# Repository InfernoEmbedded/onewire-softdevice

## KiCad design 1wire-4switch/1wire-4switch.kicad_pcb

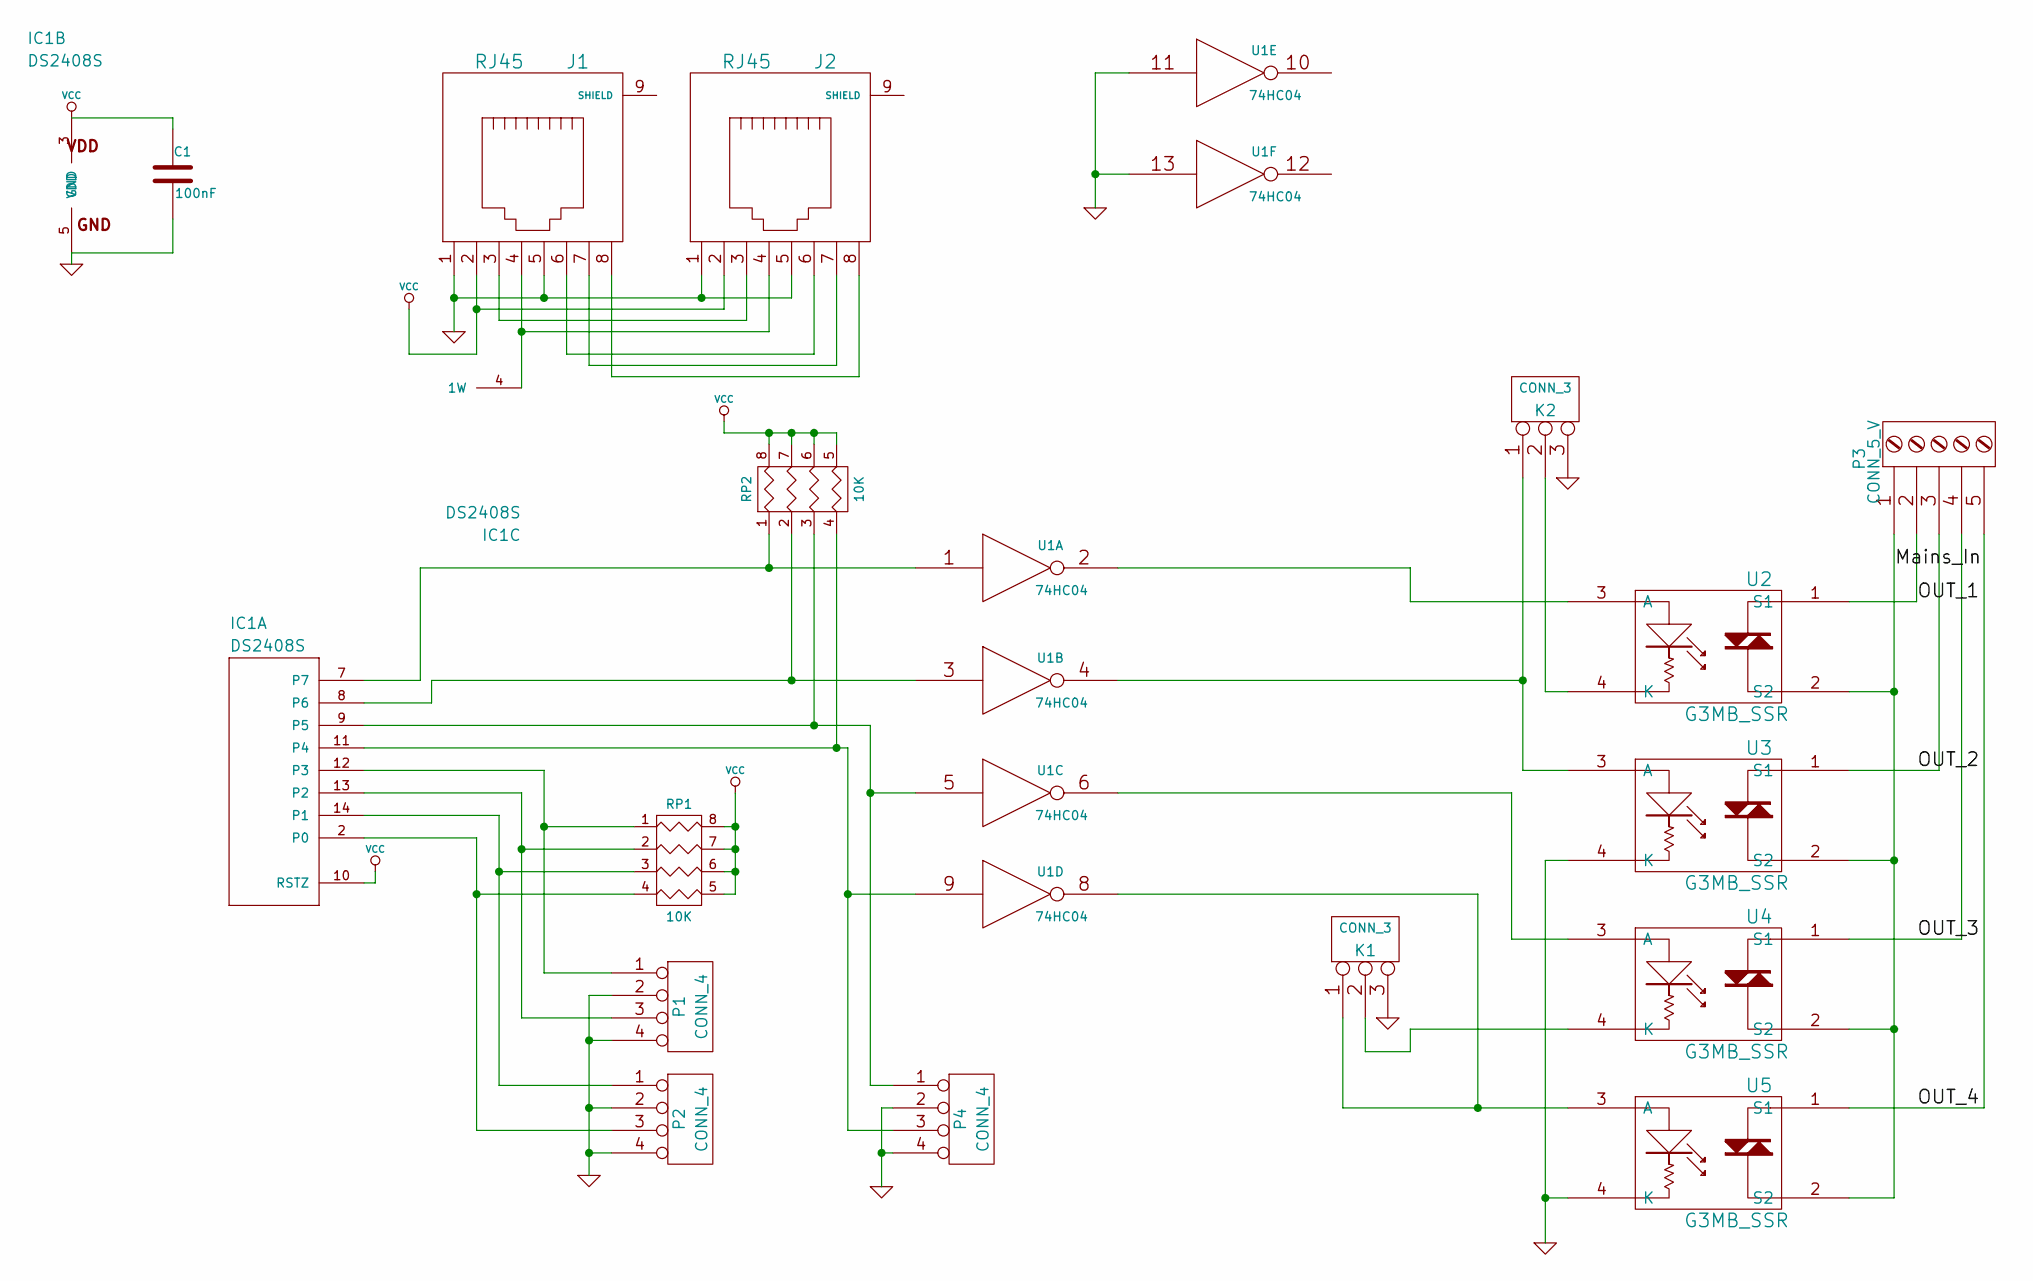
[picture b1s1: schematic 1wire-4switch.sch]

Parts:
C1: 100nF
IC1: DS2408S; 1wire-SO16
J1, J2: RJ45
K1, K2: CONN_3
P1, P2, P4: CONN_4
P3: CONN_5_V
RP1, RP2: 10K
U1: 74HC04
U2, U3, U4, U5: G3MB_SSR

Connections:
/Mains_In: P3.1, U2.2 (S2), U3.2 (S2), U4.2 (S2), U5.2 (S2)
/OUT_1: P3.2, U2.1 (S1)
/OUT_2: P3.3, U3.1 (S1)
/OUT_3: P3.4, U4.1 (S1)
/OUT_4: P3.5, U5.1 (S1)
GND: C1.2, IC1.5 (GND), J1.1, J1.5, J2.1, J2.5, K1.3, K2.3, P1.2, P1.4, P2.2, P2.4, P4.2, P4.4, U1.7 (GND), U1.11, U1.13, U3.4 (K), U5.4 (K)
unnamed: K1.1, U1.8, U5.3 (A)
unnamed: U1.6, U4.3 (A)
unnamed: IC1.7, RP2.1, U1.1
unnamed: K1.2 (PM), U4.4 (K)
unnamed: K2.1, U1.4, U3.3 (A)
unnamed: U1.2, U2.3 (A)
unnamed: K2.2 (PM), U2.4 (K)
unnamed: IC1.11 (P4), P4.3, RP2.4, U1.9
unnamed: IC1.9 (P5), P4.1, RP2.3, U1.5
unnamed: IC1.8 (P6), RP2.2, U1.3
unnamed: J1.8, J2.8
unnamed: J1.7, J2.7
unnamed: J1.6, J2.6
unnamed: IC1.4 (1W), J1.4, J2.4
unnamed: IC1.12 (P3), P1.1, RP1.1
unnamed: J1.3, J2.3
unnamed: IC1.2 (P0), P2.3, RP1.4
unnamed: IC1.14 (P1), P2.1, RP1.3
unnamed: IC1.13 (P2), P1.3, RP1.2
VCC: C1.1, IC1.3 (VDD), IC1.10 (RSTZ), J1.2, J2.2, RP1.5 (R4), RP1.6 (R3), RP1.7 (R2), RP1.8 (R1), RP2.5 (R4), RP2.6 (R3), RP2.7 (R2), RP2.8 (R1), U1.14 (VCC)

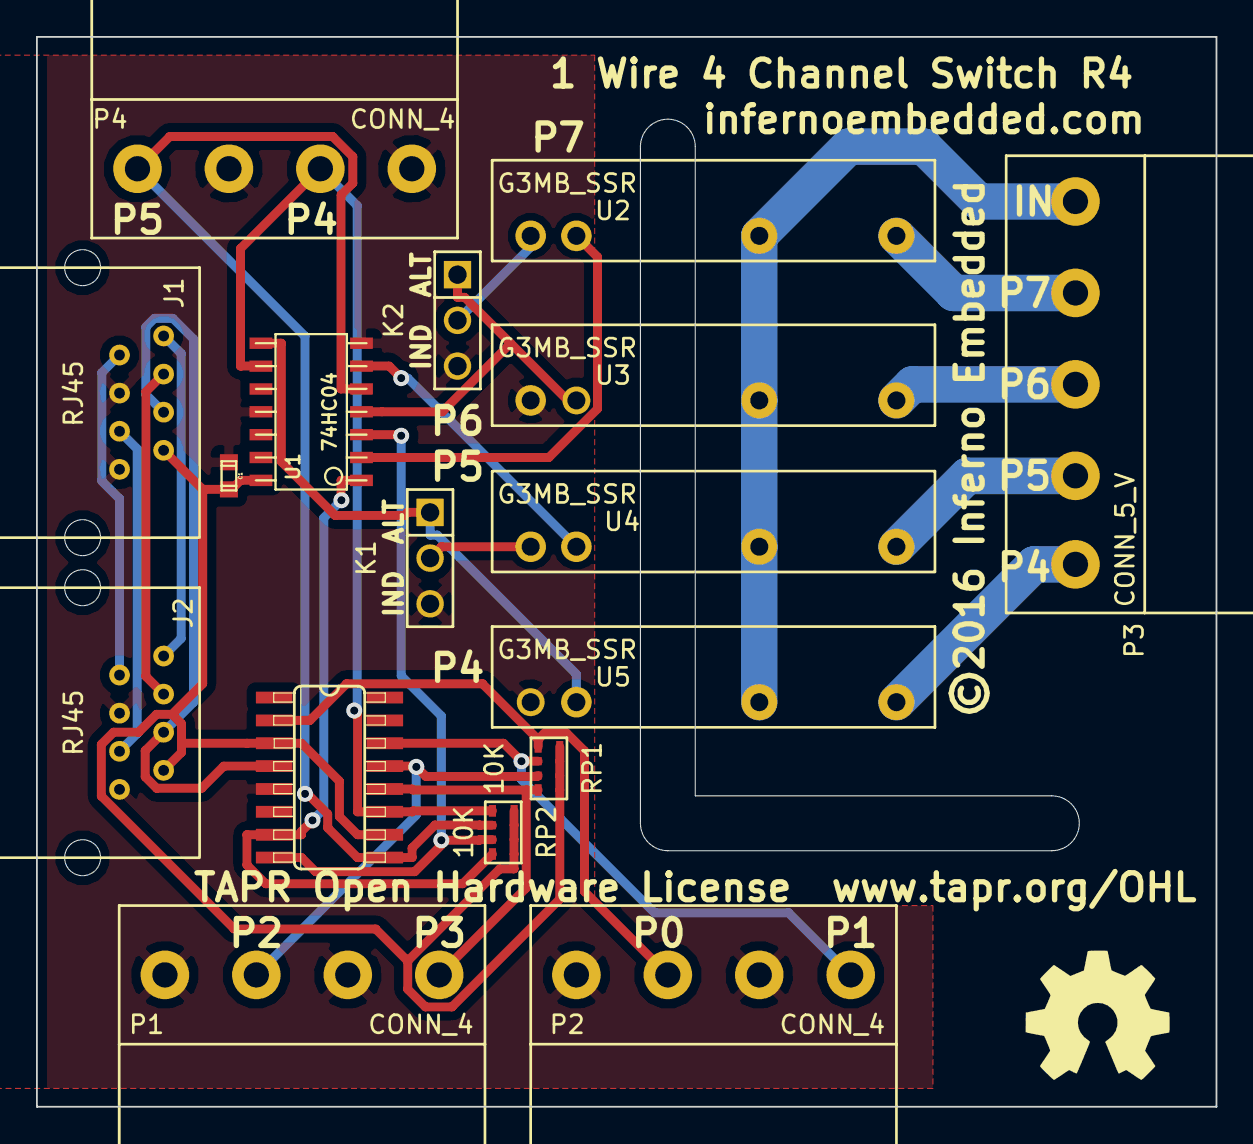
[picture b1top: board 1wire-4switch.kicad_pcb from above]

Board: 2 copper layers, 65.5 x 59.4 mm, 17 parts (0 on the bottom side), 26 nets.

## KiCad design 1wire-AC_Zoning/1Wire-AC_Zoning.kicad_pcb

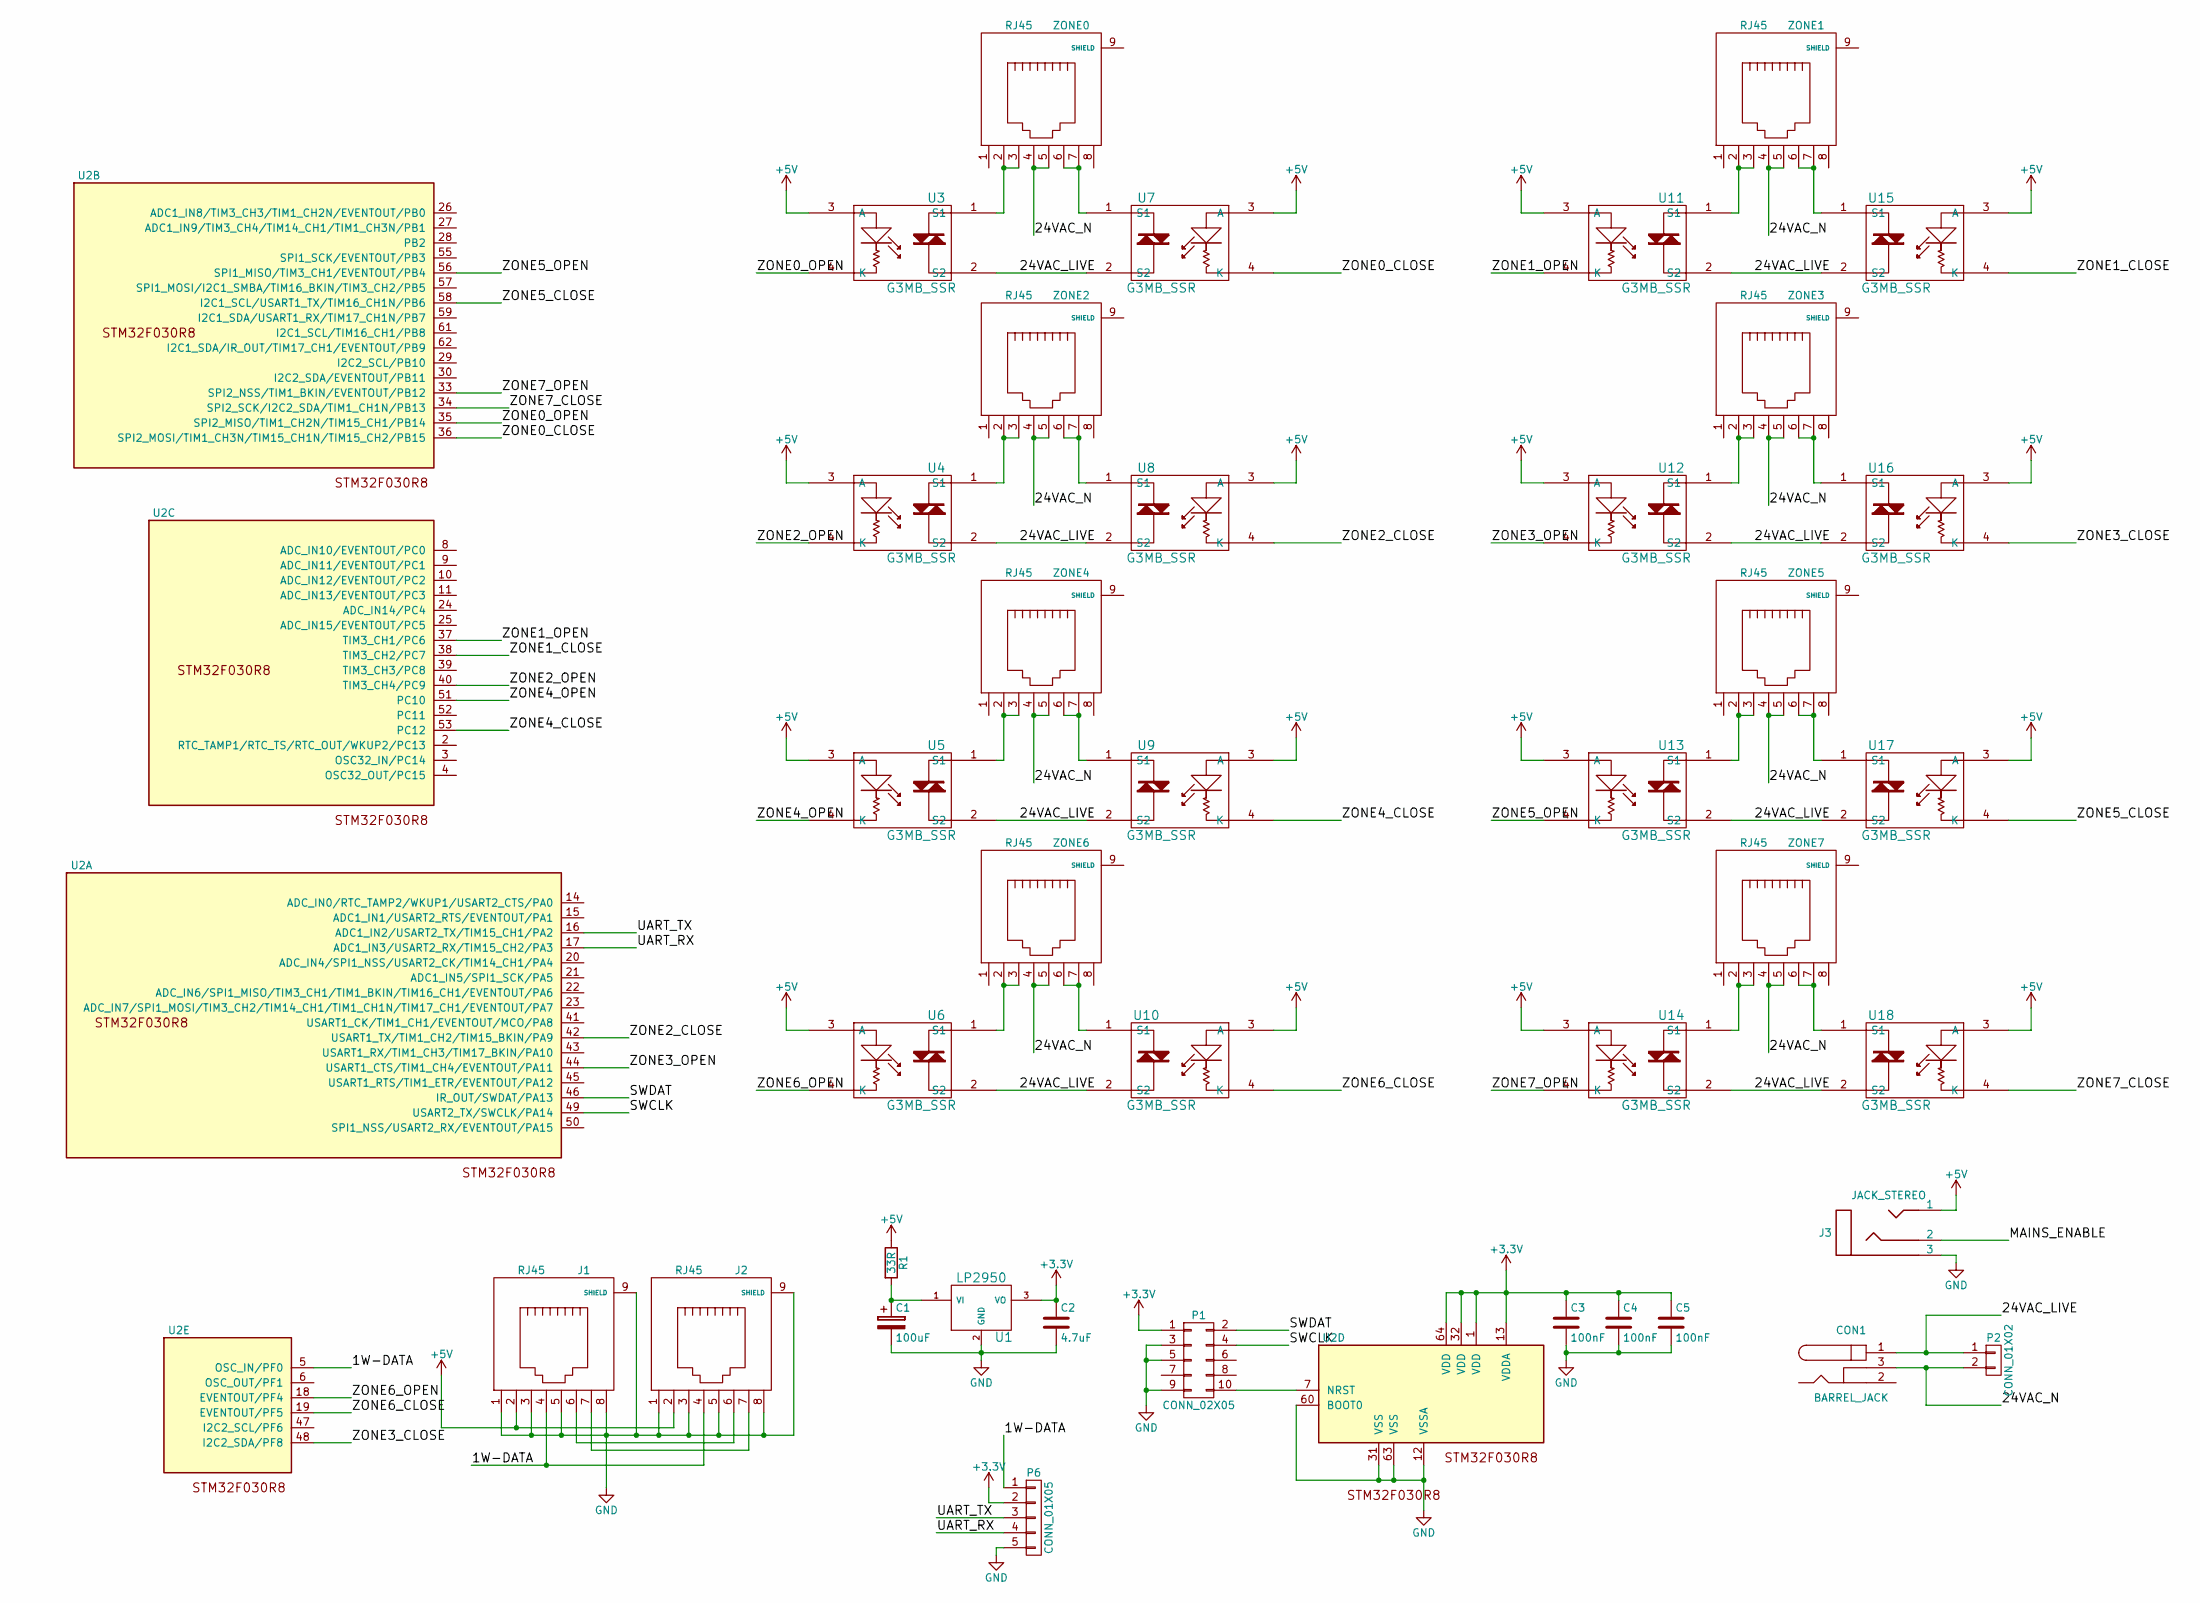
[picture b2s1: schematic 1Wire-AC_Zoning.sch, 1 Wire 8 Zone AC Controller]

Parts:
C1: 100uF; c_elec_8x6.7
C2: 4.7uF; C_0603
C3, C4, C5: 100nF; C_0603
CON1: BARREL_JACK
J1, J2: RJ45; RJ45-ChinaSMD
J3: JACK_STEREO; jack_3.5_pj313d-smt
P1: CONN_02X05; Pin_Header_Straight_SMT_02x05
P2: CONN_01X02; 2EDCK-5.08-2PIN
P6: CONN_01X05; Pin_Header_Straight_1x05_Pitch2.54mm
R1: 33R; R_0603
U1: LP2950; TO-252-2Lead
U2: STM32F030R8; LQFP-64_10x10mm_Pitch0.5mm
U3, U4, U5, U6, U7, U8, U9, U10, U11, U12, U13, U14, U15, U16, U17, U18: G3MB_SSR; G3MB
ZONE0, ZONE1, ZONE2, ZONE3, ZONE4, ZONE5, ZONE6, ZONE7: RJ45; RJ45-ChinaSMD

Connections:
+3V3: C2.1, C3.1, C4.1, C5.1, P1.1, P6.2, U1.3 (VO), U2.1 (VDD), U2.13 (VDDA), U2.32 (VDD), U2.64 (VDD)
+5V: J1.2, J2.2, J3.1, R1.1, U3.3 (A), U4.3 (A), U5.3 (A), U6.3 (A), U7.3 (A), U8.3 (A), U9.3 (A), U10.3 (A), U11.3 (A), U12.3 (A), U13.3 (A), U14.3 (A), U15.3 (A), U16.3 (A), U17.3 (A), U18.3 (A)
/1W-DATA: J1.4, J2.4, P6.1, U2.5 (OSC_IN/PF0)
/24VAC_LIVE: CON1.1, P2.1, U3.2 (S2), U4.2 (S2), U5.2 (S2), U6.2 (S2), U7.2 (S2), U8.2 (S2), U9.2 (S2), U10.2 (S2), U11.2 (S2), U12.2 (S2), U13.2 (S2), U14.2 (S2), U15.2 (S2), U16.2 (S2), U17.2 (S2), U18.2 (S2)
/24VAC_N: CON1.3, P2.2, ZONE0.4, ZONE0.5, ZONE1.4, ZONE1.5, ZONE2.4, ZONE2.5, ZONE3.4, ZONE3.5, ZONE4.4, ZONE4.5, ZONE5.4, ZONE5.5, ZONE6.4, ZONE6.5, ZONE7.4, ZONE7.5
/MAINS_ENABLE: J3.2
/SWCLK: P1.4, U2.49 (USART2_TX/SWCLK/PA14)
/SWDAT: P1.2, U2.46 (IR_OUT/SWDAT/PA13)
/UART_RX: P6.4, U2.17 (ADC1_IN3/USART2_RX/TIM15_CH2/PA3)
/UART_TX: P6.3, U2.16 (ADC1_IN2/USART2_TX/TIM15_CH1/PA2)
/ZONE0_CLOSE: U2.36 (SPI2_MOSI/TIM1_CH3N/TIM15_CH1N/TIM15_CH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), U7.4 (K)
/ZONE0_OPEN: U2.35 (SPI2_MISO/TIM1_CH2N/TIM15_CH1/PB14), U3.4 (K)
/ZONE1_CLOSE: U2.38 (TIM3_CH2/PC7), U15.4 (K)
/ZONE1_OPEN: U2.37 (TIM3_CH1/PC6), U11.4 (K)
/ZONE2_CLOSE: U2.42 (USART1_TX/TIM1_CH2/TIM15_BKIN/PA9), U8.4 (K)
/ZONE2_OPEN: U2.40 (TIM3_CH4/PC9), U4.4 (K)
/ZONE3_CLOSE: U2.48 (I2C2_SDA/PF8), U16.4 (K)
/ZONE3_OPEN: U2.44 (USART1_CTS/TIM1_CH4/EVENTOUT/PA11), U12.4 (K)
/ZONE4_CLOSE: U2.53 (PC12), U9.4 (K)
/ZONE4_OPEN: U2.51 (PC10), U5.4 (K)
/ZONE5_CLOSE: U2.58 (I2C1_SCL/USART1_TX/TIM16_CH1N/PB6), U17.4 (K)
/ZONE5_OPEN: U2.56 (SPI1_MISO/TIM3_CH1/EVENTOUT/PB4), U13.4 (K)
/ZONE6_CLOSE: U2.19 (EVENTOUT/PF5), U10.4 (K)
/ZONE6_OPEN: U2.18 (EVENTOUT/PF4), U6.4 (K)
/ZONE7_CLOSE: U2.34 (SPI2_SCK/I2C2_SDA/TIM1_CH1N/PB13), U18.4 (K)
/ZONE7_OPEN: U2.33 (SPI2_NSS/TIM1_BKIN/EVENTOUT/PB12), U14.4 (K)
GND: C1.2, C2.2, C3.2, C4.2, C5.2, J1.1, J1.3, J1.5, J1.8, J1.9 (SHIELD), J2.1, J2.3, J2.5, J2.8, J2.9 (SHIELD), J3.3, P1.3, P1.5, P1.9, P6.5, U1.2 (GND), U2.12 (VSSA), U2.31 (VSS), U2.60 (BOOT0), U2.63 (VSS)
unnamed: C1.1, R1.2, U1.1 (VI)
unnamed: J1.6, J2.6
unnamed: J1.7, J2.7
unnamed: P1.10, U2.7 (NRST)
unnamed: U3.1 (S1), ZONE0.2, ZONE0.3
unnamed: U4.1 (S1), ZONE2.2, ZONE2.3
unnamed: U5.1 (S1), ZONE4.2, ZONE4.3
unnamed: U6.1 (S1), ZONE6.2, ZONE6.3
unnamed: U7.1 (S1), ZONE0.6, ZONE0.7
unnamed: U8.1 (S1), ZONE2.6, ZONE2.7
unnamed: U9.1 (S1), ZONE4.6, ZONE4.7
unnamed: U10.1 (S1), ZONE6.6, ZONE6.7
unnamed: U11.1 (S1), ZONE1.2, ZONE1.3
unnamed: U12.1 (S1), ZONE3.2, ZONE3.3
unnamed: U13.1 (S1), ZONE5.2, ZONE5.3
unnamed: U14.1 (S1), ZONE7.2, ZONE7.3
unnamed: U15.1 (S1), ZONE1.6, ZONE1.7
unnamed: U16.1 (S1), ZONE3.6, ZONE3.7
unnamed: U17.1 (S1), ZONE5.6, ZONE5.7
unnamed: U18.1 (S1), ZONE7.6, ZONE7.7

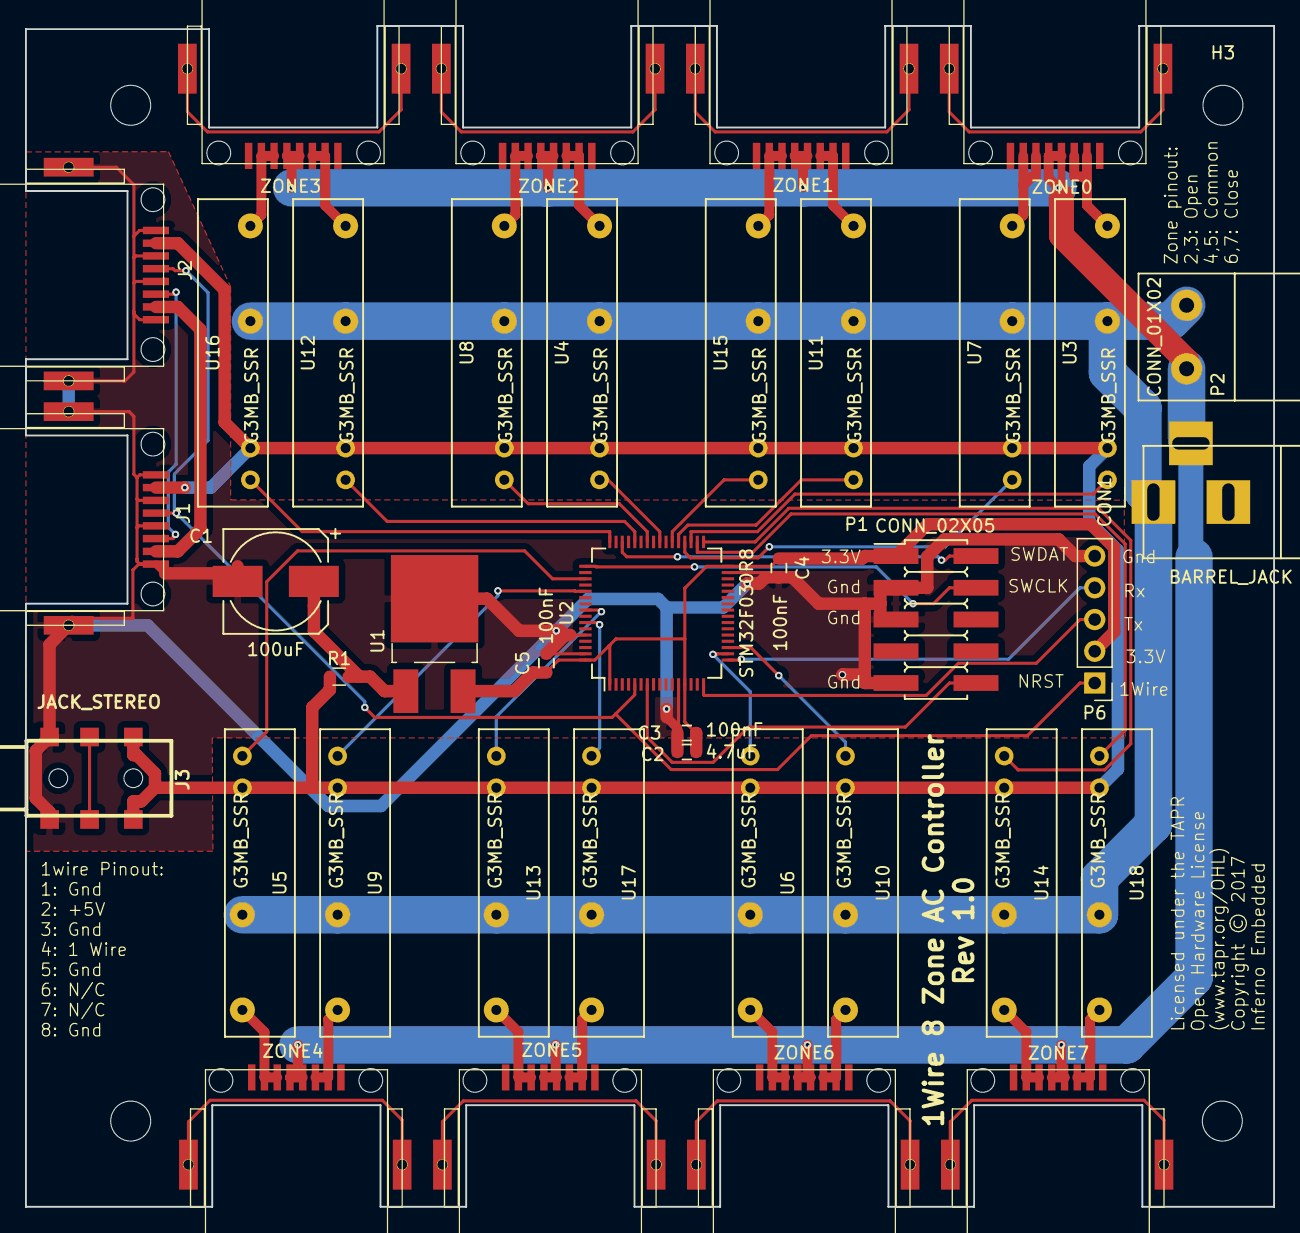
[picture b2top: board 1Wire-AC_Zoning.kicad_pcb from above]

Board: 2 copper layers, 99.9 x 94.5 mm, 43 parts (0 on the bottom side), 46 nets.

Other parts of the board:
H1, H2, H3, H4: MountingHole_3.2mm_M3

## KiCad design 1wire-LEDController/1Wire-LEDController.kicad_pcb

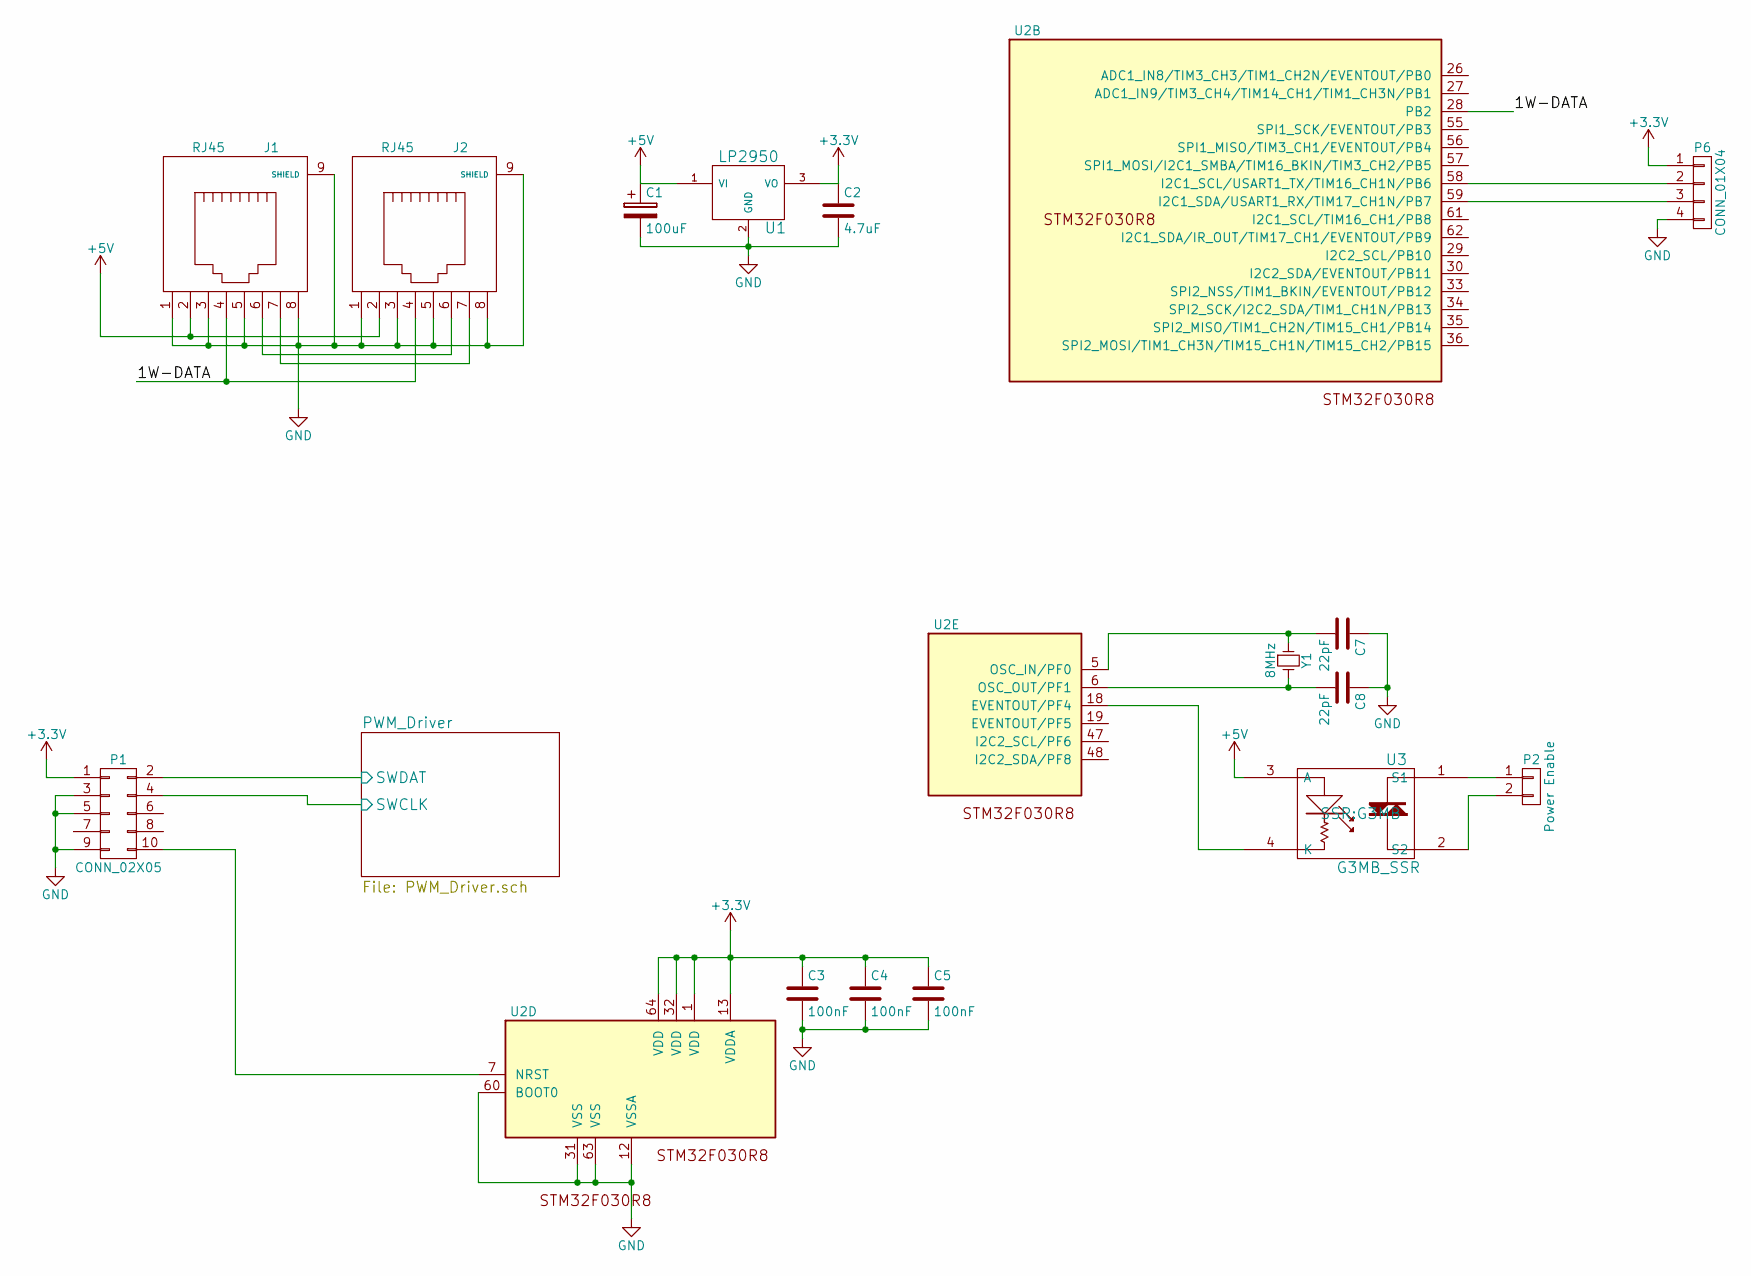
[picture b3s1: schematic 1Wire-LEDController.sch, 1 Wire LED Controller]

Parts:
C1: 100uF; c_elec_8x6.7
C2: 4.7uF; C_0603
C3, C4, C5: 100nF; C_0603
C7, C8: 22pF; C_0603
J1, J2: RJ45; RJ45-ChinaSMD
P1: CONN_02X05; Pin_Header_Straight_SMT_02x05
P2: Power Enable; 2EDCK-5.08-2PIN
P6: CONN_01X04; Pin_Header_Straight_1x04
U1: LP2950; D2PAK
U2: STM32F030R8; LQFP-64_10x10mm_Pitch0.5mm
U3: G3MB_SSR; G3MB
Y1: 8MHz; Crystal_HC49-SD_SMD

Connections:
+3V3: C2.1, C3.1, C4.1, C5.1, P1.1, P6.1, U1.3 (VO), U2.1 (VDD), U2.13 (VDDA), U2.32 (VDD), U2.64 (VDD)
+5V: C1.1, J1.2, J2.2, U1.1 (VI), U3.3 (A)
/1W-DATA: J1.4, J2.4, U2.28 (PB2)
/PWM_Driver/SWCLK: P1.4; also elsewhere on the board
/PWM_Driver/SWDAT: P1.2; also elsewhere on the board
GND: C1.2, C2.2, C3.2, C4.2, C5.2, C7.1, C8.1, J1.1, J1.3, J1.5, J1.8, J1.9 (SHIELD), J2.1, J2.3, J2.5, J2.8, J2.9 (SHIELD), P1.3, P1.5, P1.9, P6.4, U1.2 (GND), U2.12 (VSSA), U2.31 (VSS), U2.60 (BOOT0), U2.63 (VSS); also elsewhere on the board
unnamed: C7.2, U2.5 (OSC_IN/PF0), Y1.1
unnamed: C8.2, U2.6 (OSC_OUT/PF1), Y1.2
unnamed: J1.6, J2.6
unnamed: J1.7, J2.7
unnamed: P1.10, U2.7 (NRST)
unnamed: P2.1, U3.1 (S1)
unnamed: P2.2, U3.2 (S2)
unnamed: P6.2, U2.58 (I2C1_SCL/USART1_TX/TIM16_CH1N/PB6)
unnamed: P6.3, U2.59 (I2C1_SDA/USART1_RX/TIM17_CH1N/PB7)
unnamed: U2.18 (EVENTOUT/PF4), U3.4 (K)

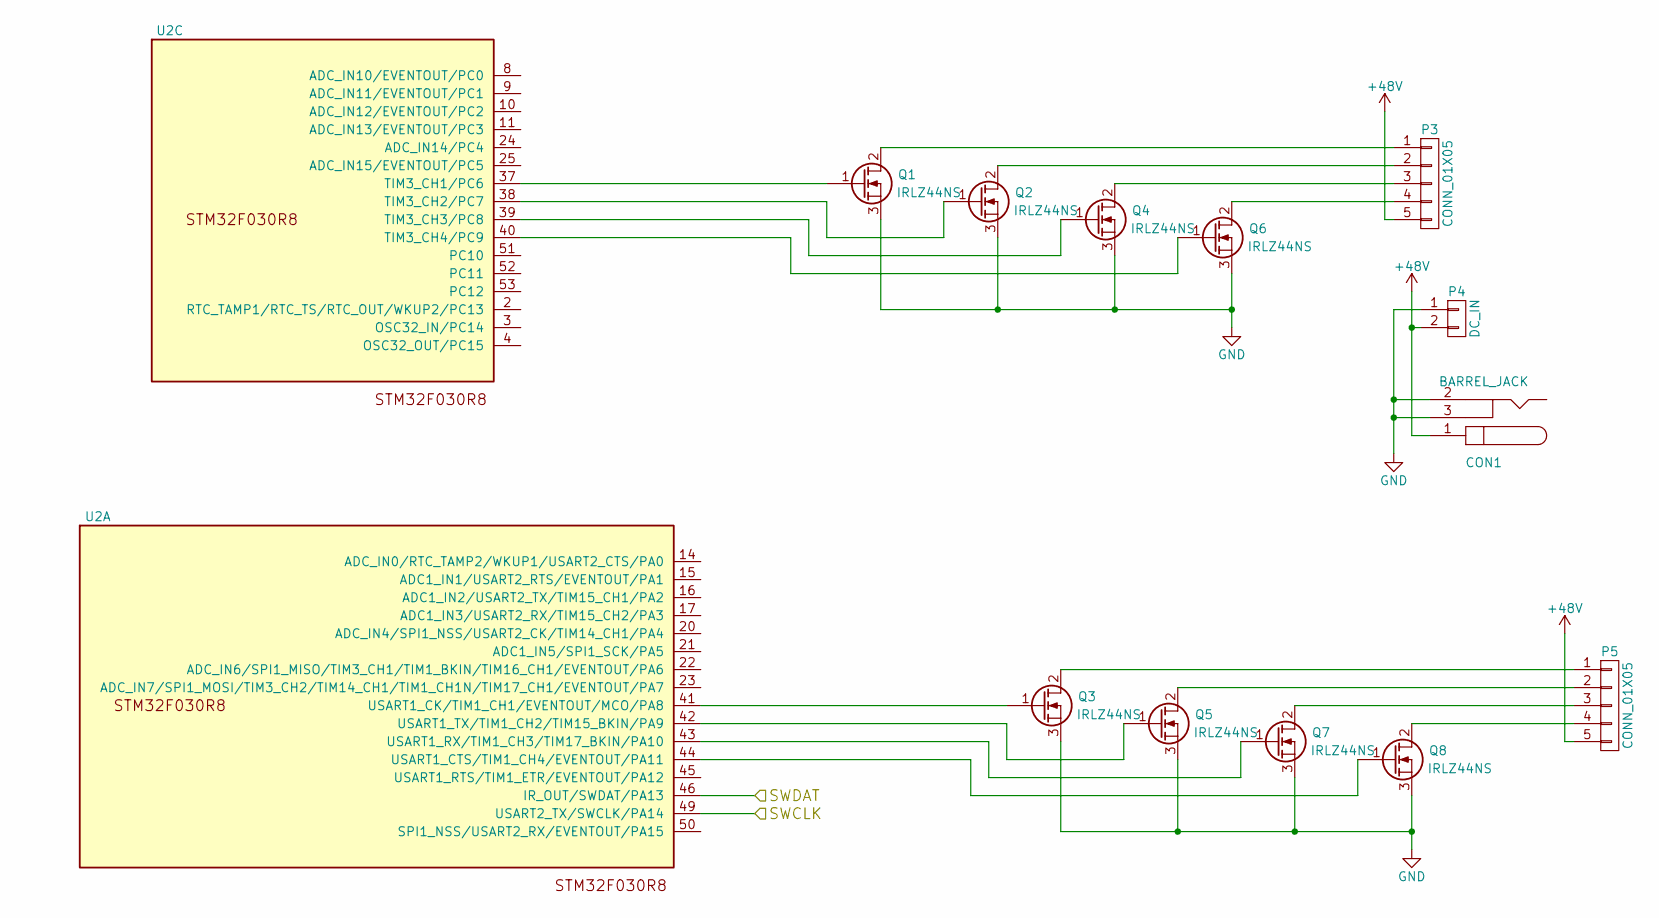
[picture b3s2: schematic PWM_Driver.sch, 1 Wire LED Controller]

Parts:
CON1: BARREL_JACK
P3, P5: CONN_01X05; 2EDCK-5.08-5PIN
P4: DC_IN; 2EDCK-5.08-2PIN
Q1, Q2, Q3, Q4, Q5, Q6, Q7, Q8: IRLZ44NS; D2PAK
U2: STM32F030R8; LQFP-64_10x10mm_Pitch0.5mm

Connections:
+48V: CON1.1, P3.5, P4.2, P5.5
/PWM_Driver/SWCLK: U2.49 (USART2_TX/SWCLK/PA14); also elsewhere on the board
/PWM_Driver/SWDAT: U2.46 (IR_OUT/SWDAT/PA13); also elsewhere on the board
GND: CON1.2, CON1.3, P4.1, Q1.3 (S), Q2.3 (S), Q3.3 (S), Q4.3 (S), Q5.3 (S), Q6.3 (S), Q7.3 (S), Q8.3 (S); also elsewhere on the board
unnamed: P3.1, Q1.2 (D)
unnamed: P3.2, Q2.2 (D)
unnamed: P3.3, Q4.2 (D)
unnamed: P3.4, Q6.2 (D)
unnamed: P5.1, Q3.2 (D)
unnamed: P5.2, Q5.2 (D)
unnamed: P5.3, Q7.2 (D)
unnamed: P5.4, Q8.2 (D)
unnamed: Q1.1 (G), U2.37 (TIM3_CH1/PC6)
unnamed: Q2.1 (G), U2.38 (TIM3_CH2/PC7)
unnamed: Q3.1 (G), U2.41 (USART1_CK/TIM1_CH1/EVENTOUT/MCO/PA8)
unnamed: Q4.1 (G), U2.39 (TIM3_CH3/PC8)
unnamed: Q5.1 (G), U2.42 (USART1_TX/TIM1_CH2/TIM15_BKIN/PA9)
unnamed: Q6.1 (G), U2.40 (TIM3_CH4/PC9)
unnamed: Q7.1 (G), U2.43 (USART1_RX/TIM1_CH3/TIM17_BKIN/PA10)
unnamed: Q8.1 (G), U2.44 (USART1_CTS/TIM1_CH4/EVENTOUT/PA11)

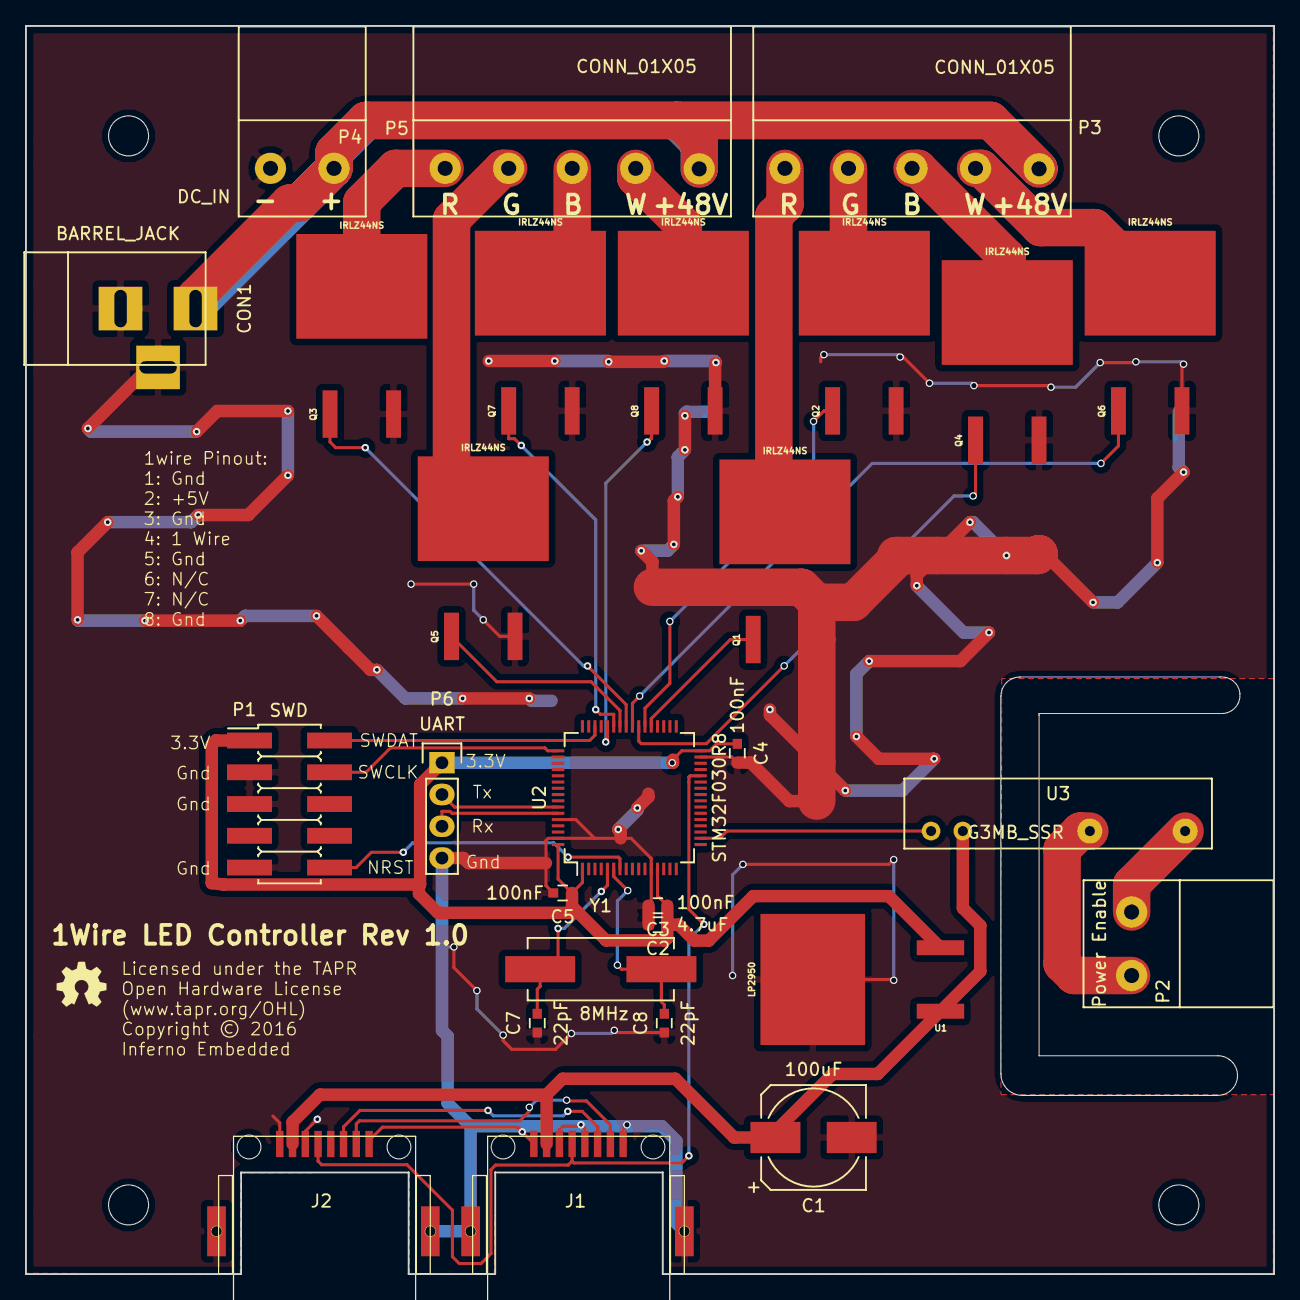
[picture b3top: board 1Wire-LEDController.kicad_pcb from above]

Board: 2 copper layers, 99.8 x 99.8 mm, 32 parts (0 on the bottom side), 33 nets.

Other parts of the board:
REF1, REF2, REF3, REF4: MountingHole_3.2mm_M3

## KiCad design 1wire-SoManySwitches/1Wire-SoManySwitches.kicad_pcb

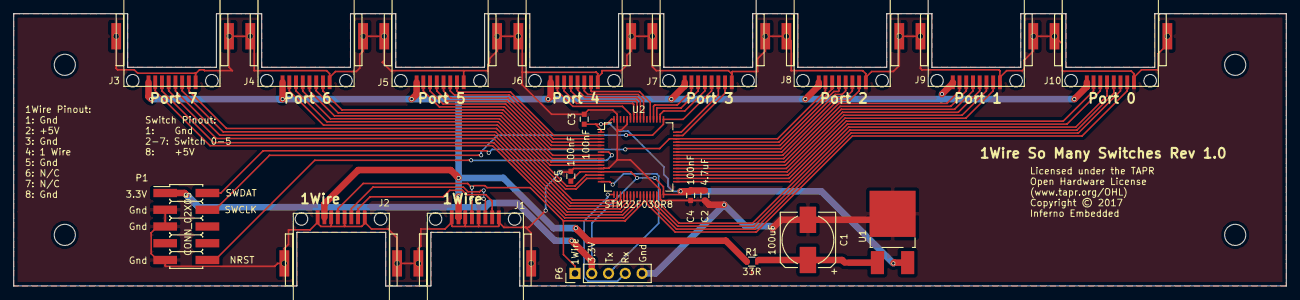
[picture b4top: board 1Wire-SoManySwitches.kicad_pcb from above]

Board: 2 copper layers, 192.9 x 41.3 mm, 24 parts (0 on the bottom side), 58 nets.

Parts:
C1: 100uF; c_elec_8x6.7
C2: 4.7uF; C_0603
C3, C4, C5: 100nF; C_0603
J1, J2, J3, J4, J5, J6, J7, J8, J9, J10: RJ45; RJ45-ChinaSMD
P1: CONN_02X05; Pin_Header_Straight_SMT_02x05
P6: CONN_01X05; Pin_Header_Straight_1x05_Pitch2.54mm
R1: 33R; R_0603
REF1, REF2, REF3, REF4: MountingHole_3.2mm_M3
U1: LP2950; TO-252-2Lead
U2: STM32F030R8; LQFP-64_10x10mm_Pitch0.5mm

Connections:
+3V3: C2.1, C3.1, C4.1, C5.1, P1.1, P6.2, U1.3, U2.1, U2.13, U2.32, U2.64
+5V: J1.2, J2.2, J3.8, J4.8, J5.8, J6.8, J7.8, J8.8, J9.8, J10.8, R1.1
/1W-DATA: J1.4, J2.4, P6.1, U2.26
/J3_0: J3.2, U2.19
/J3_1: J3.3, U2.20
/J3_2: J3.4, U2.21
/J3_3: J3.5, U2.22
/J3_4: J3.6, U2.23
/J3_5: J3.7, U2.25
/J4_0: J4.2, U2.9
/J4_1: J4.3, U2.10
/J4_2: J4.4, U2.11
/J4_3: J4.5, U2.14
/J4_4: J4.6, U2.15
/J4_5: J4.7, U2.18
/J5_0: J5.2, U2.2
/J5_1: J5.3, U2.3
/J5_2: J5.4, U2.4
/J5_3: J5.5, U2.5
/J5_4: J5.6, U2.6
/J5_5: J5.7, U2.8
/J6_0: J6.2, U2.53
/J6_1: J6.3, U2.55
/J6_2: J6.4, U2.56
/J6_3: J6.5, U2.57
/J6_4: J6.6, U2.58
/J6_5: J6.7, U2.59
/J7_0: J7.2, U2.47
/J7_1: J7.3, U2.48
/J7_2: J7.4, P1.4, U2.49
/J7_3: J7.5, U2.50
/J7_4: J7.6, U2.51
/J7_5: J7.7, U2.52
/J8_0: J8.2, U2.41
/J8_1: J8.3, U2.42
/J8_2: J8.4, U2.43
/J8_3: J8.5, U2.44
/J8_4: J8.6, U2.45
/J8_5: J8.7, P1.2, U2.46
/J9_0: J9.2, U2.35
/J9_1: J9.3, U2.36
/J9_2: J9.4, U2.37
/J9_3: J9.5, U2.38
/J9_4: J9.6, U2.39
/J9_5: J9.7, U2.40
/J10_0: J10.2, U2.27
/J10_1: J10.3, U2.28
/J10_2: J10.4, U2.29
/J10_3: J10.5, U2.30
/J10_4: J10.6, U2.33
/J10_5: J10.7, U2.34
/UART_RX: P6.4, U2.17
/UART_TX: P6.3, U2.16
GND: C1.2, C2.2, C3.2, C4.2, C5.2, J1.1, J1.3, J1.5, J1.8, J1.9, J2.1, J2.3, J2.5, J2.8, J2.9, J3.1, J3.9, J4.1, J4.9, J5.1, J5.9, J6.1, J6.9, J7.1, J7.9, J8.1, J8.9, J9.1, J9.9, J10.1, J10.9, P1.3, P1.5, P1.9, P6.5, U1.2, U2.12, U2.31, U2.60, U2.63
unnamed: C1.1, R1.2, U1.1
unnamed: J1.6, J2.6
unnamed: J1.7, J2.7
unnamed: P1.10, U2.7

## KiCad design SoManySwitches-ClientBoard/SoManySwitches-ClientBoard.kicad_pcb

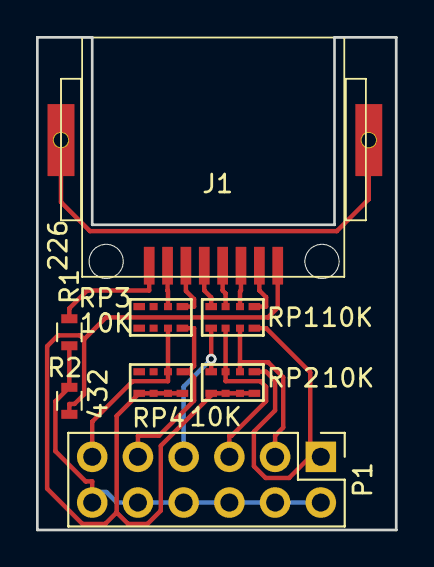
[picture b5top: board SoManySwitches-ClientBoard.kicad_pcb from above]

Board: 2 copper layers, 19.9 x 27.4 mm, 8 parts (0 on the bottom side), 15 nets.

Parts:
J1: RJ45; RJ45-ChinaSMD
P1: CONN_02X06; Pin_Header_Straight_2x06_Pitch2.54mm
R1: 226; R_0603
R2: 432; R_0603
RP1, RP2, RP3, RP4: 10K; 0603_Pack4

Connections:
+3V3: P1.2, P1.4, P1.6, P1.8, P1.10, P1.12, R1.2, R2.1
+5V: J1.8, R1.1
GND: J1.1, R2.2, RP2.5, RP2.6, RP2.7, RP2.8, RP4.5, RP4.6, RP4.7, RP4.8
unnamed: J1.2, RP1.4
unnamed: J1.3, RP1.3
unnamed: J1.4, RP1.2
unnamed: J1.5, RP1.1
unnamed: J1.6, RP3.4
unnamed: J1.7, RP3.3
unnamed: P1.1, RP1.5, RP2.4
unnamed: P1.3, RP1.6, RP2.3
unnamed: P1.5, RP1.7, RP2.2
unnamed: P1.7, RP1.8, RP2.1
unnamed: P1.9, RP3.5, RP4.4
unnamed: P1.11, RP3.6, RP4.3

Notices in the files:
1wire-4switch/1wire-4switch.kicad_pcb:
TAPR Open Hardware License  www.tapr.org/OHL
©2016 Inferno Embedded
1wire-AC_Zoning/1Wire-AC_Zoning.kicad_pcb:
Licensed under the TAPR Open Hardware License (www.tapr.org/OHL)
Copyright © 2017 Inferno Embedded
1wire-LEDController/1Wire-LEDController.kicad_pcb:
Copyright © 2016 Inferno Embedded
devices/Aircon_Zone_Controller/1Wire-AC_Zoning.sch:
Copyright © 2018 Inferno Embedded
